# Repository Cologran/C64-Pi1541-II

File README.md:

# C64 PI1541-II

This is a light modified version of the C64-PI1541-II from tebl. (https://github.com/tebl/C64-Pi1541-II)

Changes "Module": 
1) Power Connector moved from the left side to the back side
2) PCB cut like in "Faceplate" und "Backplate"
3) moved the speaker 1 mm down and left
4) reroute conducting paths around the speaker
5) reroute conducting paths for the power jack and the display
6) remove the soldering holes for the display (-> Faceplate)

Changes "Faceplate":
1) redesign the visable cupper 
2) remove the mounting holes for the display

Changes "FaceplateB":
1) redesign the visable cupper 
2) remove the mounting holes for the display

Changes "Backplate":
1) redesign the visable cupper 

You still can use the build instructions and the BOM from https://github.com/tebl/C64-Pi1541-II

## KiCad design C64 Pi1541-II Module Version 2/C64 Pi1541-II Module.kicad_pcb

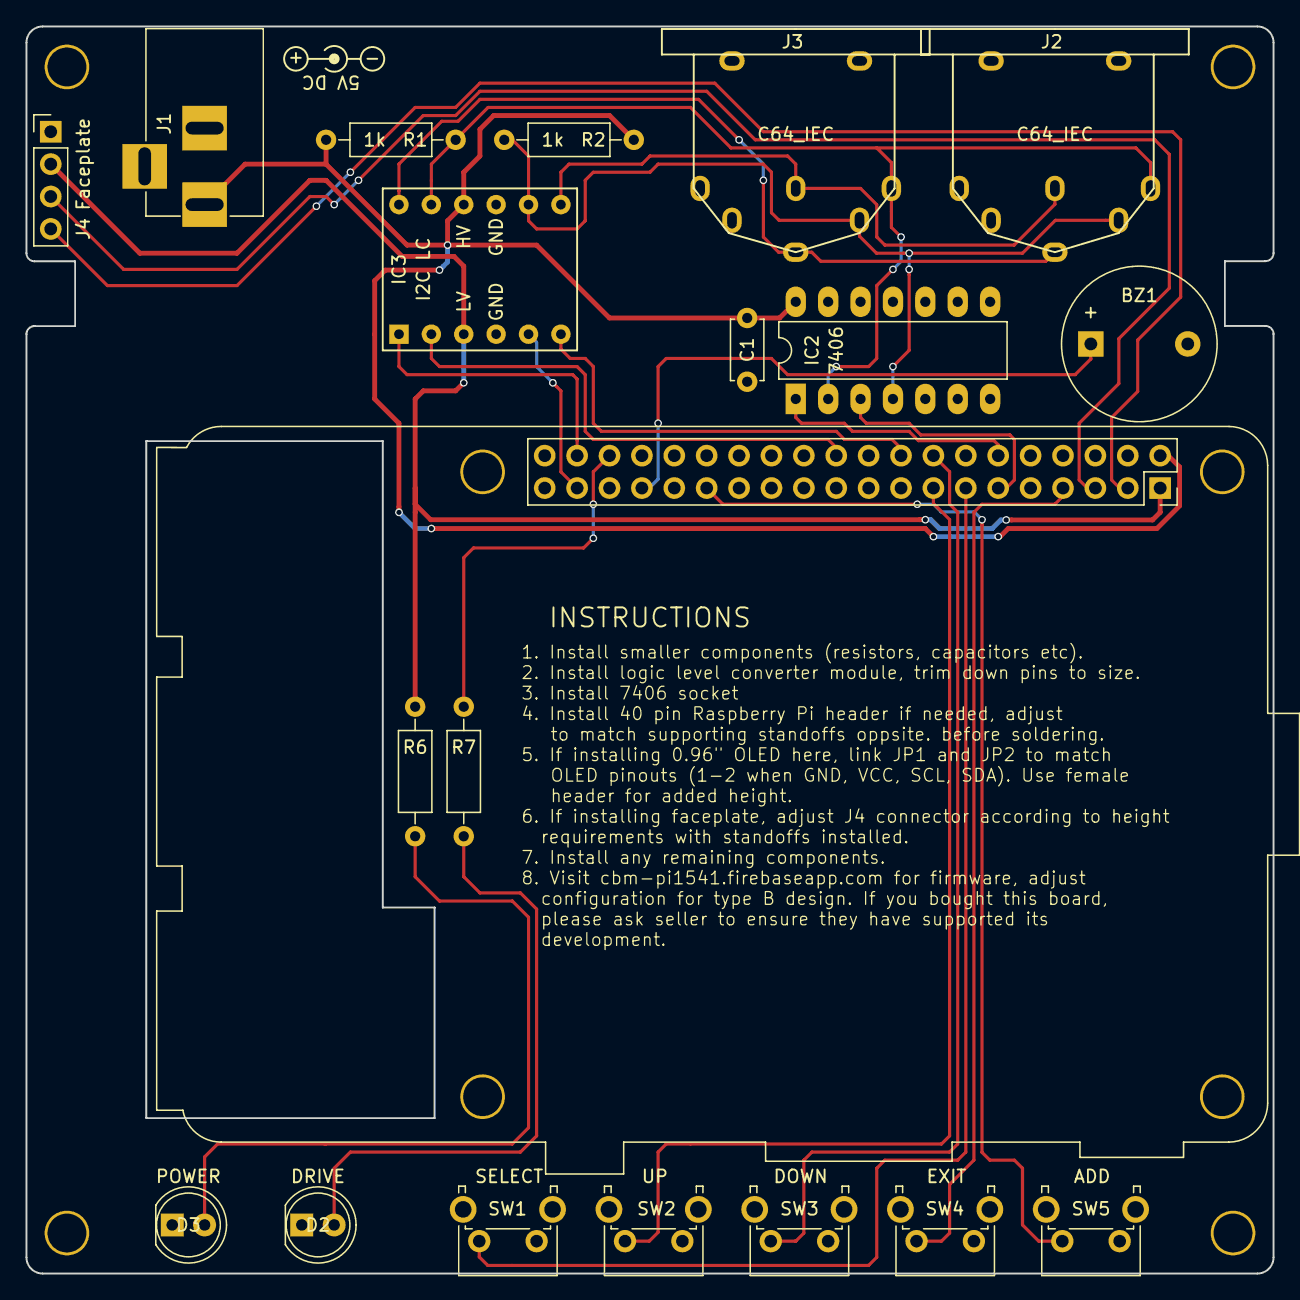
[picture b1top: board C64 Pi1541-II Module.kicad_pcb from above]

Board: 2 copper layers, 97.8 x 97.8 mm, 24 parts (0 on the bottom side), 24 nets.

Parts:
A1: Raspberry PI; Raspberry_Pi_3B_Socketed_THT_FaceDown_MountingHoles
BZ1: Buzzer; Buzzer_12x9.5RM7.6
C1: 100nF; C_Disc_D4.7mm_W2.5mm_P5.00mm
D2: DRIVE; LED_D5.0mm
D3: POWER; LED_D5.0mm
IC2: 7406; DIP-14_W7.62mm_LongPads
IC3: I2C LC; 4CH_I2C_Level_Converter
J1: DC IN; BARREL_JACK
J2, J3: C64_IEC
J4: Faceplate; Pin_Header_Straight_1x04_Pitch2.54mm
M1, M2, M3, M4: Mounting; M3
R1, R2: 1k; R_Axial_DIN0207_L6.3mm_D2.5mm_P10.16mm_Horizontal
R6, R7: 330; R_Axial_DIN0207_L6.3mm_D2.5mm_P10.16mm_Horizontal
SW1: SELECT; SW_Tactile_SPST_Angled_PTS645Vx39-2LFS
SW2: UP; SW_Tactile_SPST_Angled_PTS645Vx39-2LFS
SW3: DOWN; SW_Tactile_SPST_Angled_PTS645Vx39-2LFS
SW4: EXIT; SW_Tactile_SPST_Angled_PTS645Vx39-2LFS
SW5: ADD; SW_Tactile_SPST_Angled_PTS645Vx39-2LFS

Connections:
+3V3: A1.1, IC3.3, J4.2, R6.2
+5V: A1.2, C1.1, IC2.14, IC3.10, J1.1, R1.1, R2.1
C64_ATN: IC3.7, J2.3, J3.3
C64_CLK: IC2.4, IC3.8, J2.4, J3.4, R2.2
C64_DATA: IC2.2, IC3.11, J2.5, J3.5, R1.2
C64_RST: IC3.12, J2.6, J3.6
GND: A1.6, A1.9, A1.14, A1.20, A1.25, A1.30, A1.34, A1.39, BZ1.2, C1.2, D2.1, D3.1, IC2.7, IC3.4, IC3.9, J1.2, J1.3, J2.2, J2.7, J2.8, J3.2, J3.7, J3.8, J4.1, SW1.1, SW2.1, SW3.1, SW4.1, SW5.1
I2C_SCL: A1.5, J4.3
I2C_SDA: A1.3, J4.4
unnamed: A1.33, BZ1.1
unnamed: D2.2, R7.1
unnamed: D3.2, R6.1
RPI_ATN: A1.18, IC3.6
RPI_CLK_IN: A1.37, IC3.5
RPI_CLK_OUT: A1.11, IC2.3
RPI_DATA_IN: A1.22, IC3.2
RPI_DATA_OUT: A1.12, IC2.1
RPI_LED: A1.36, R7.2
RPI_RST: A1.38, IC3.1
SW1: A1.13, SW1.2
SW2: A1.15, SW2.2
SW3: A1.16, SW3.2
SW4: A1.7, SW4.2
SW5: A1.29, SW5.2

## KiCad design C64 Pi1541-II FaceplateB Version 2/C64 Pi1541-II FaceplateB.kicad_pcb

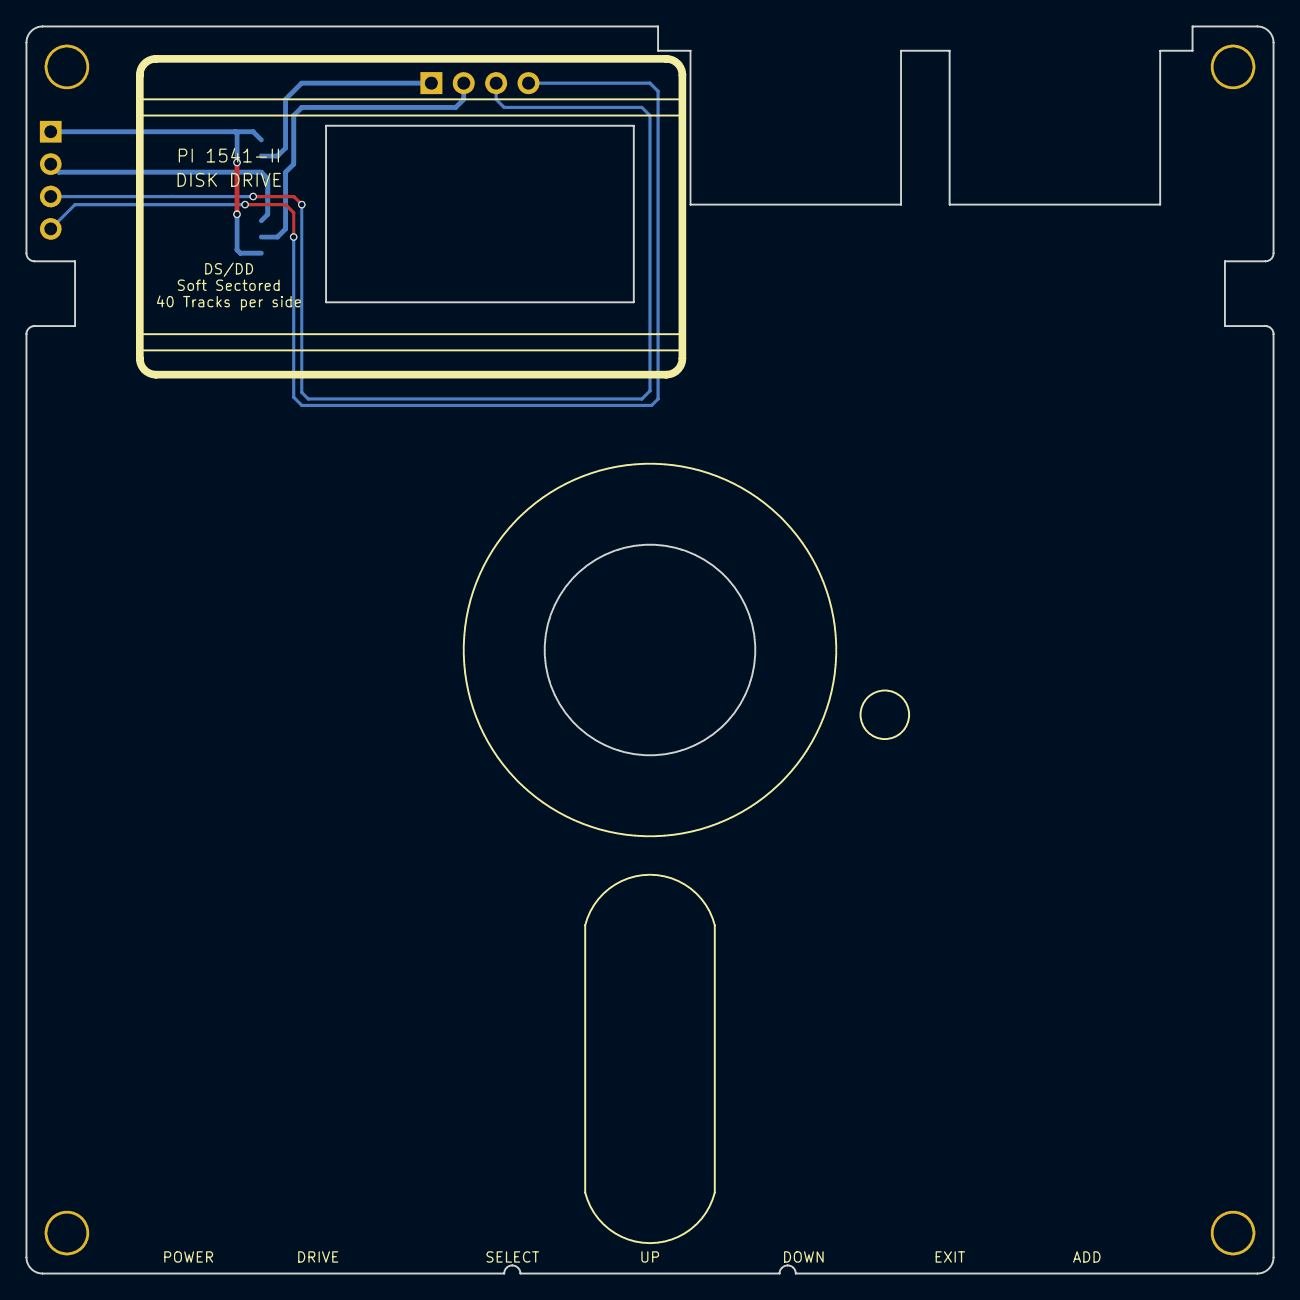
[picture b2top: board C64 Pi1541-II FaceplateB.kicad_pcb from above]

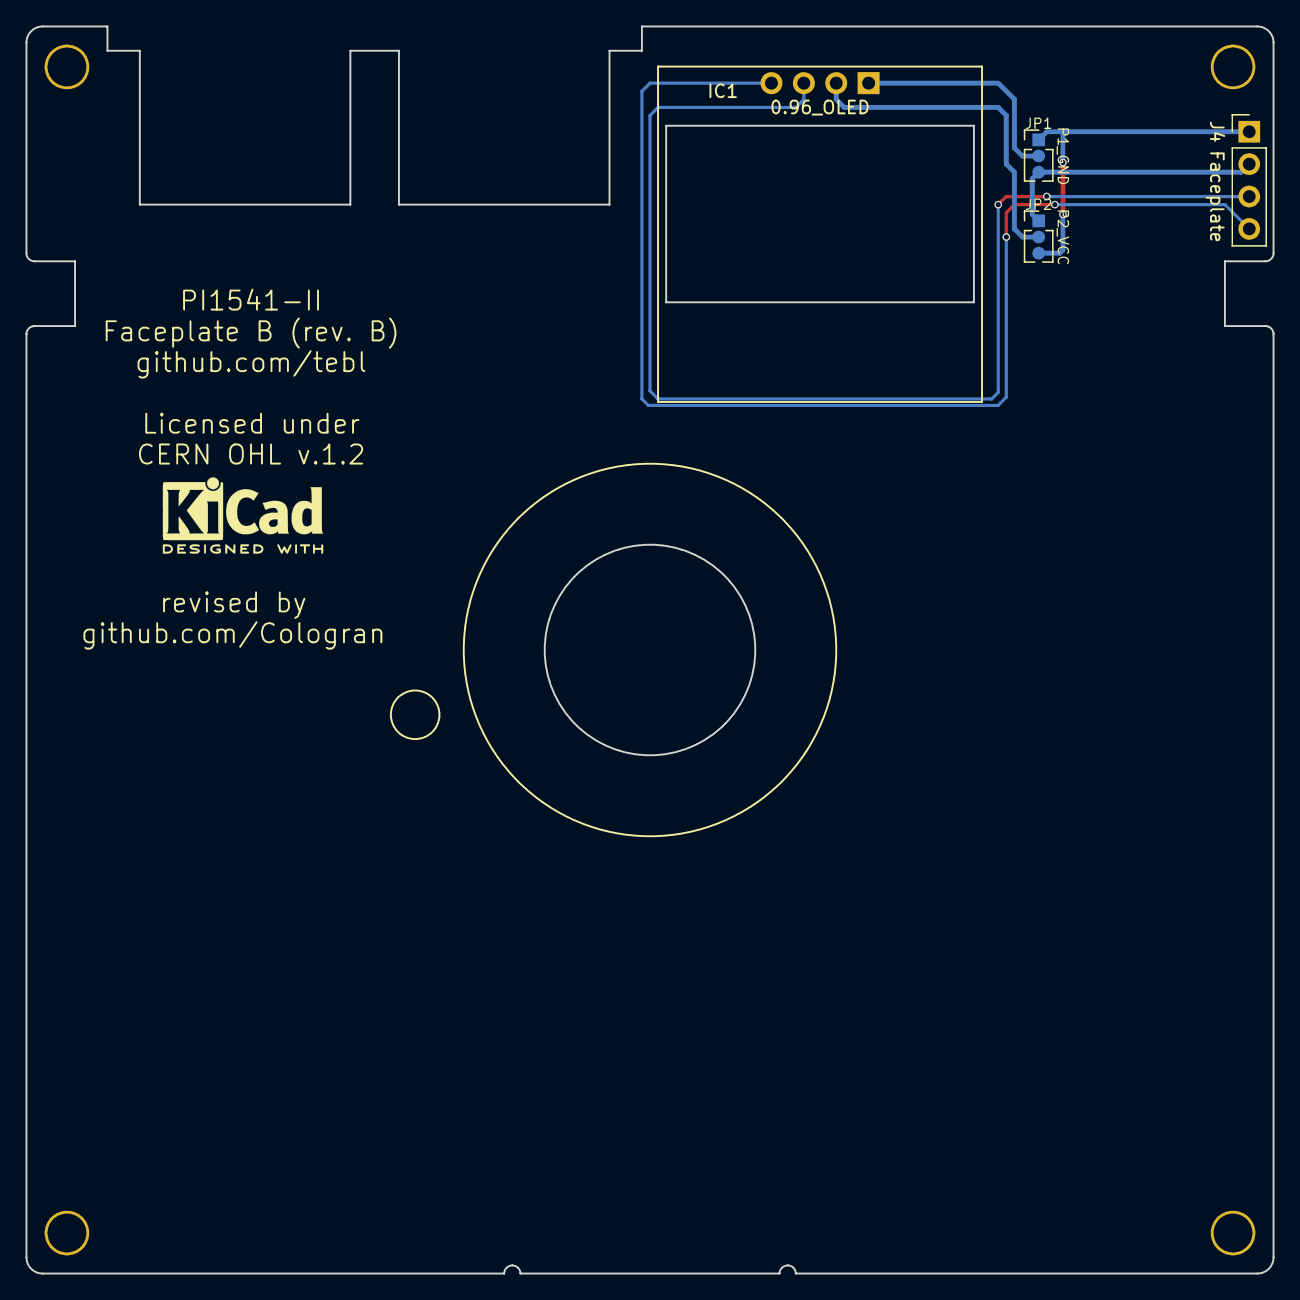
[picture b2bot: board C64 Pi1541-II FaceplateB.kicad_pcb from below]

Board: 2 copper layers, 97.8 x 97.8 mm, 8 parts (3 on the bottom side), 6 nets.

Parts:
IC1: 0.96_OLED; 0.96_I2C_OLED_NEW
J4: Faceplate; Pin_Header_Straight_1x04_Pitch2.54mm
JP1: P1_GND; OLED_SEL
JP2: P2_VCC; OLED_SEL
M1, M2, M3, M4: Mounting; M3

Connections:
+3V3: J4.2, JP1.3, JP2.1
GND: J4.1, JP1.1, JP2.3
I2C_SCL: IC1.3, J4.3
I2C_SDA: IC1.4, J4.4
unnamed: IC1.1, JP1.2
unnamed: IC1.2, JP2.2

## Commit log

2020-12-30 Create C64 Pi1541-II Backplate Version 2
2020-12-30 Create test

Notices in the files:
C64 Pi1541-II FaceplateB Version 2/C64 Pi1541-II FaceplateB.kicad_pcb:
Licensed under
CERN OHL v.1.2
